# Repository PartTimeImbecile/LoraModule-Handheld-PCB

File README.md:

# LoraModule-Project-PCB
An ultra cheap pcb I created for combining an ESP32S3 Supermini and a wide variety of Lora SMD chips such as the RA-01SH, this design is not meant to be used as a relay/Transmission node for extended periods of time due to the strain on the esp32s internal voltage converter, while it will function and do so quite decently, my other project is much better built for this while being only mildly more expensive. 

WARNING- DO NOT USE WITH RA-01SH-P, The P model is a higher drain edition of the module im using specially made for transmiting, it draws about 1A (at +31 Dbm) and would fry the esp if used with this pcb and it also has a different pinout, it includes a vccpa pin which accepts 5v directly for a higher transmit power. In summary, check the max draw and ensure its around 300-400 Milliamps at most.

I ordered my pcb from pcbway, it cost me around 5 euro for 5 of them and delivery was quite cheap, so if anyone wants to replicate it, its not too expensive.

The RA chips can be found on aliexpress for around 3 euro each and the s3 supermini is around 2 euro if bought directly from the maker on aliexpress

## Compatibility Notes
* **LoRa Modules:** Many other RA-xxx chips share the same footprint but ensure to check this for yourself

* **Microcontrollers:** Along with this, the supermini s3 shares a footprint with many other superminis, but once again this is at user discretion and some code modification may be needed, but as far as i know they should be similar enough to work almost without any issues.

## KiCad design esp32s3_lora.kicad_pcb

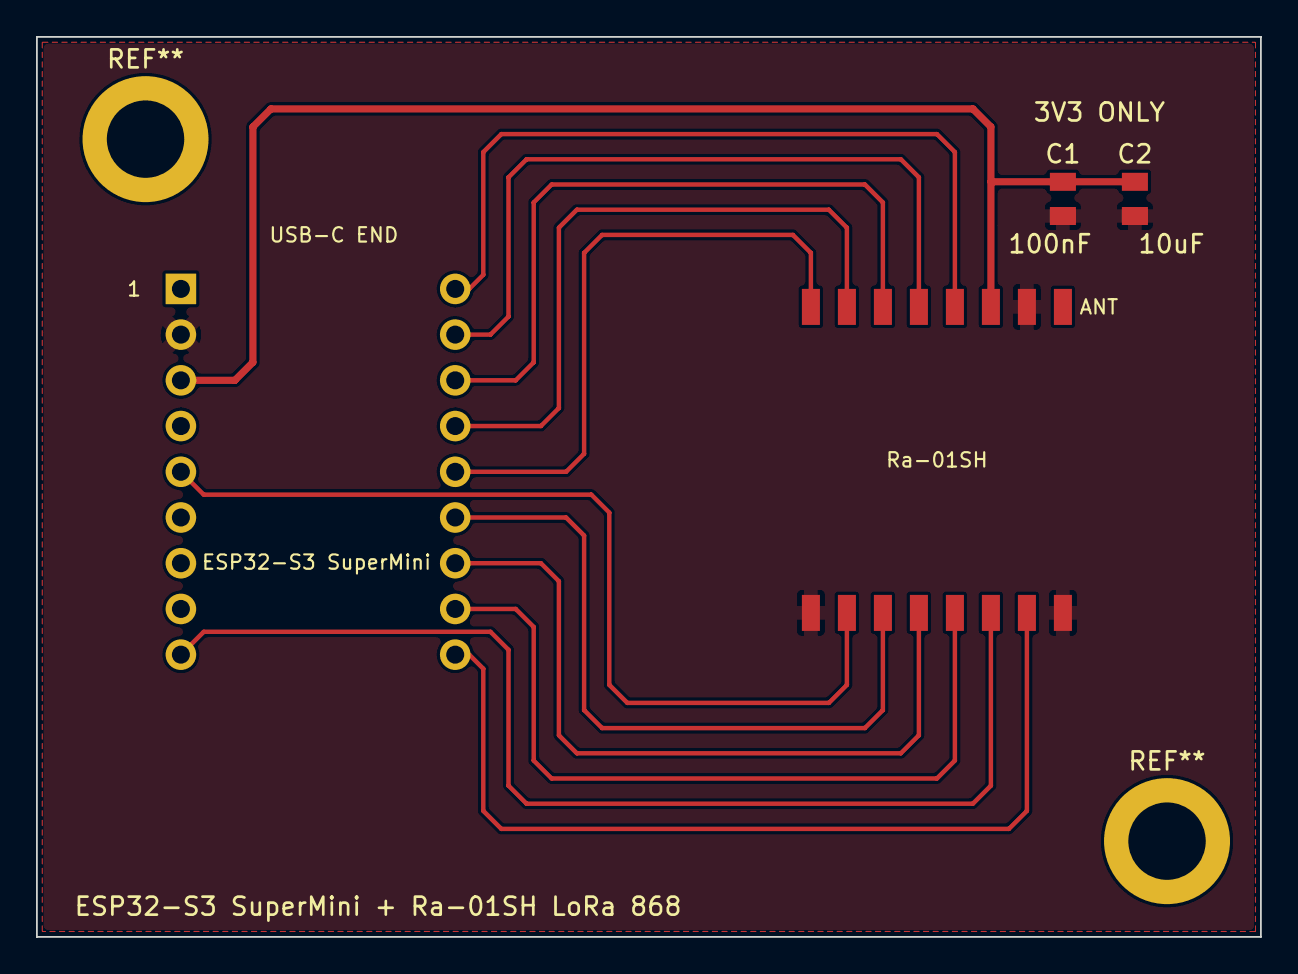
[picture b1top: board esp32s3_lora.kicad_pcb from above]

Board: 2 copper layers, 68.0 x 50.0 mm, 4 parts (0 on the bottom side), 13 nets.

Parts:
C1: 100nF; C_0805_Vertical
C2: 10uF; C_0805_Vertical
U1: ESP32-S3 SuperMini; ESP32-S3_SuperMini_Headers
U2: Ra-01SH; Ai-Thinker_Ra-01SH

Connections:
+3V3: C1.1, C2.1, U1.3, U2.3
/BUSY: U1.5, U2.10
/DIO1: U1.12, U2.6
/DIO2: U1.13, U2.7
/DIO3: U1.14, U2.8
/MISO: U1.17, U2.13
/MOSI: U1.9, U2.14
/NSS: U1.18, U2.15
/RST: U1.10, U2.4
/RXEN: U1.15, U2.11
/SCK: U1.16, U2.12
/TXEN: U1.11, U2.5
GND: C1.2, C2.2, U1.2, U2.2, U2.9, U2.16
